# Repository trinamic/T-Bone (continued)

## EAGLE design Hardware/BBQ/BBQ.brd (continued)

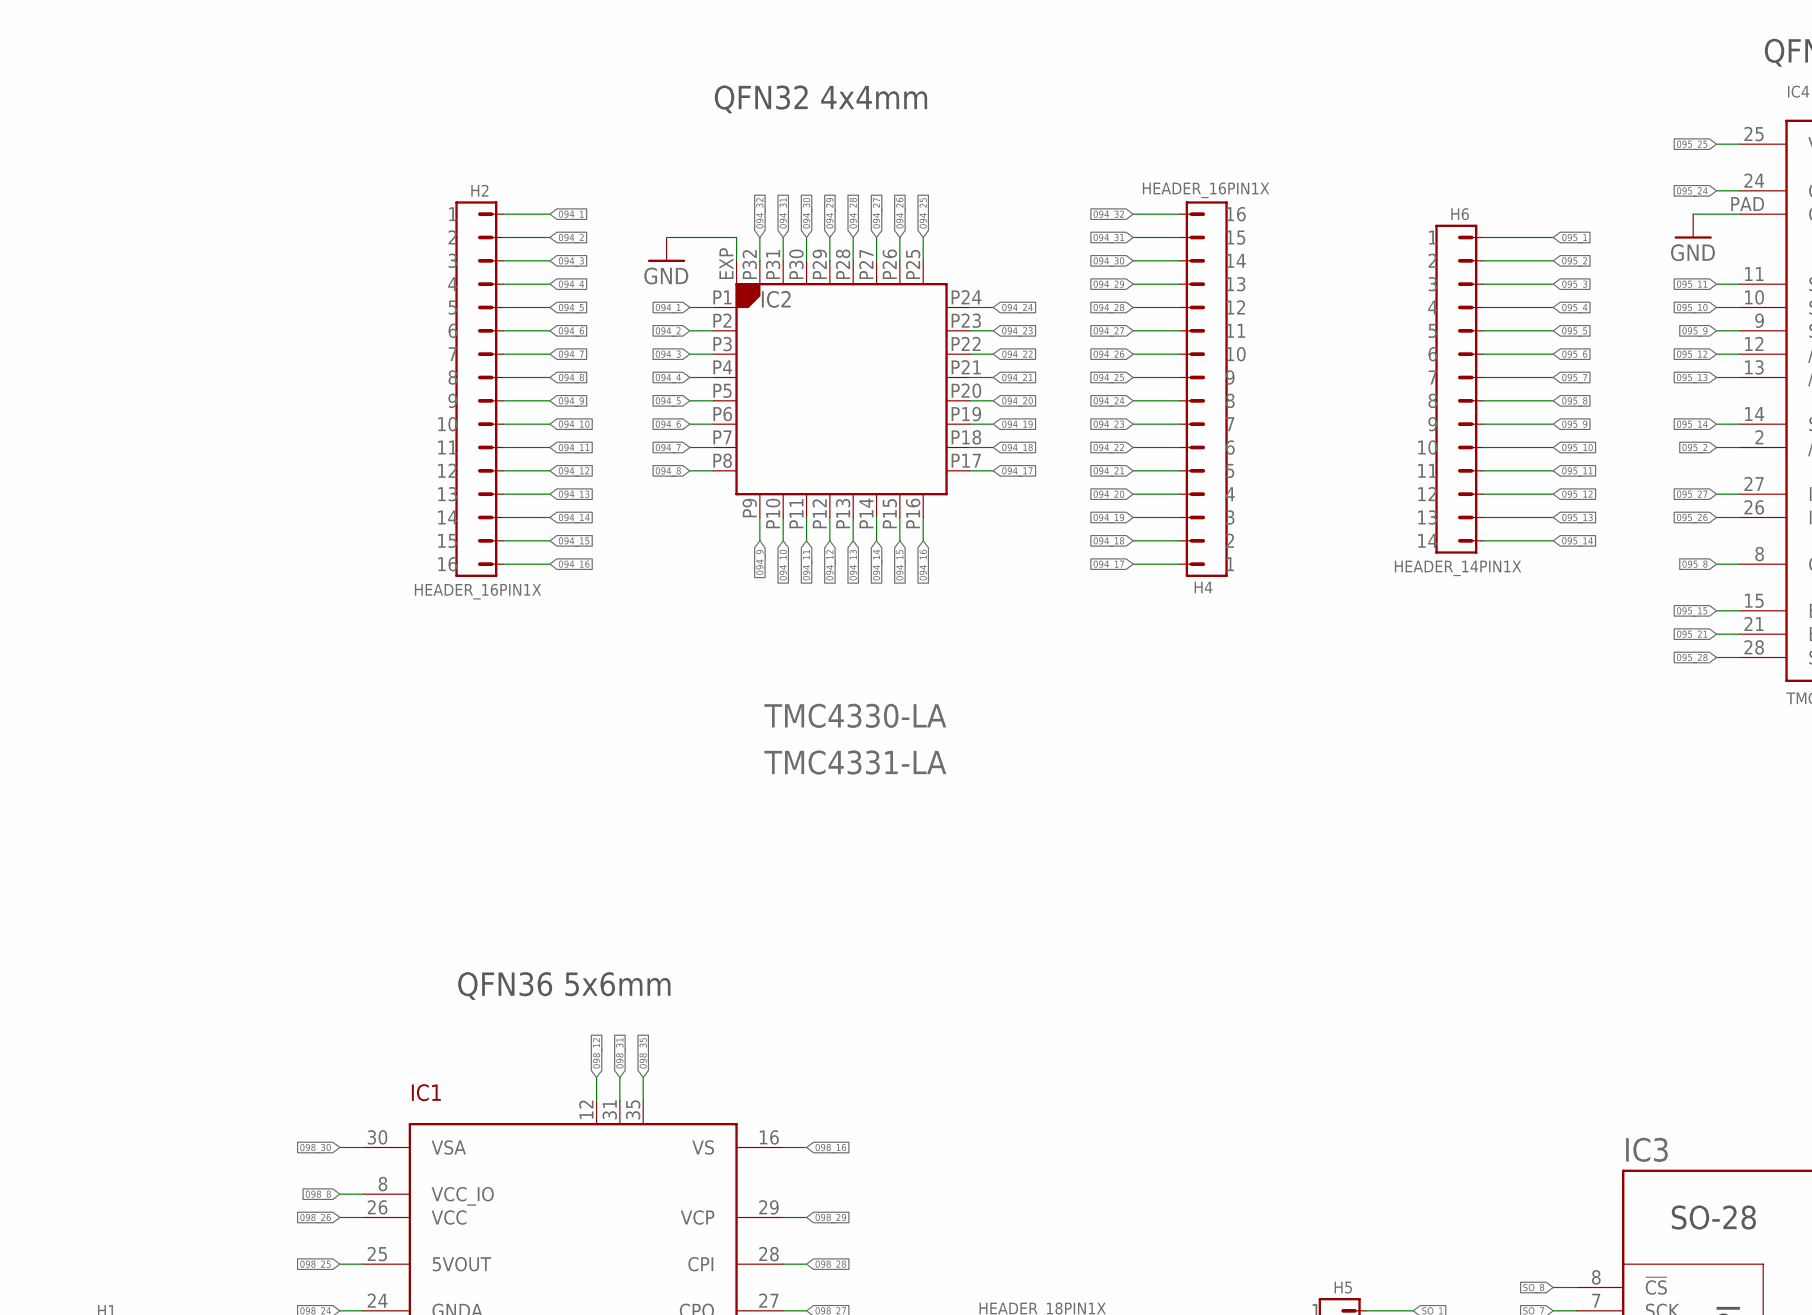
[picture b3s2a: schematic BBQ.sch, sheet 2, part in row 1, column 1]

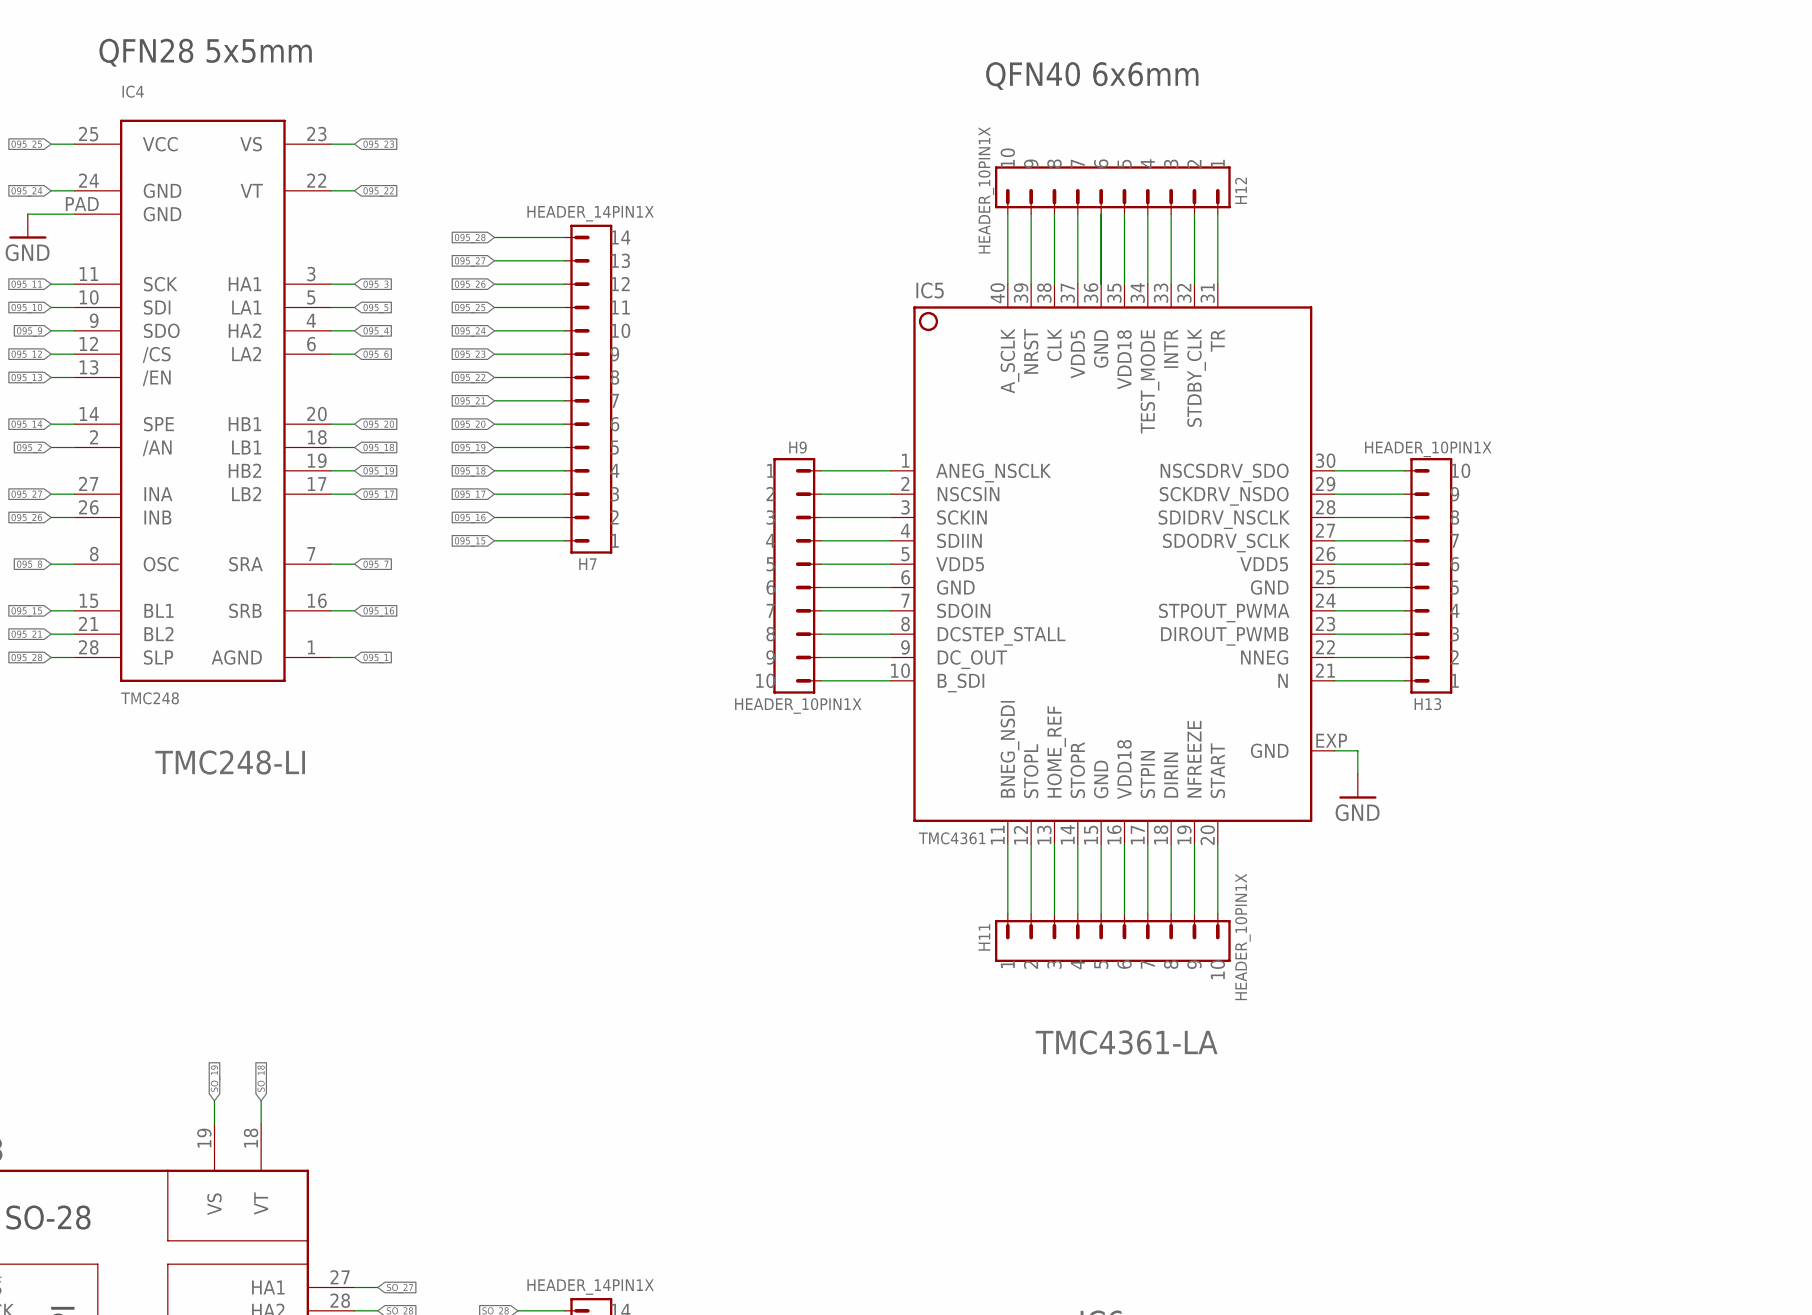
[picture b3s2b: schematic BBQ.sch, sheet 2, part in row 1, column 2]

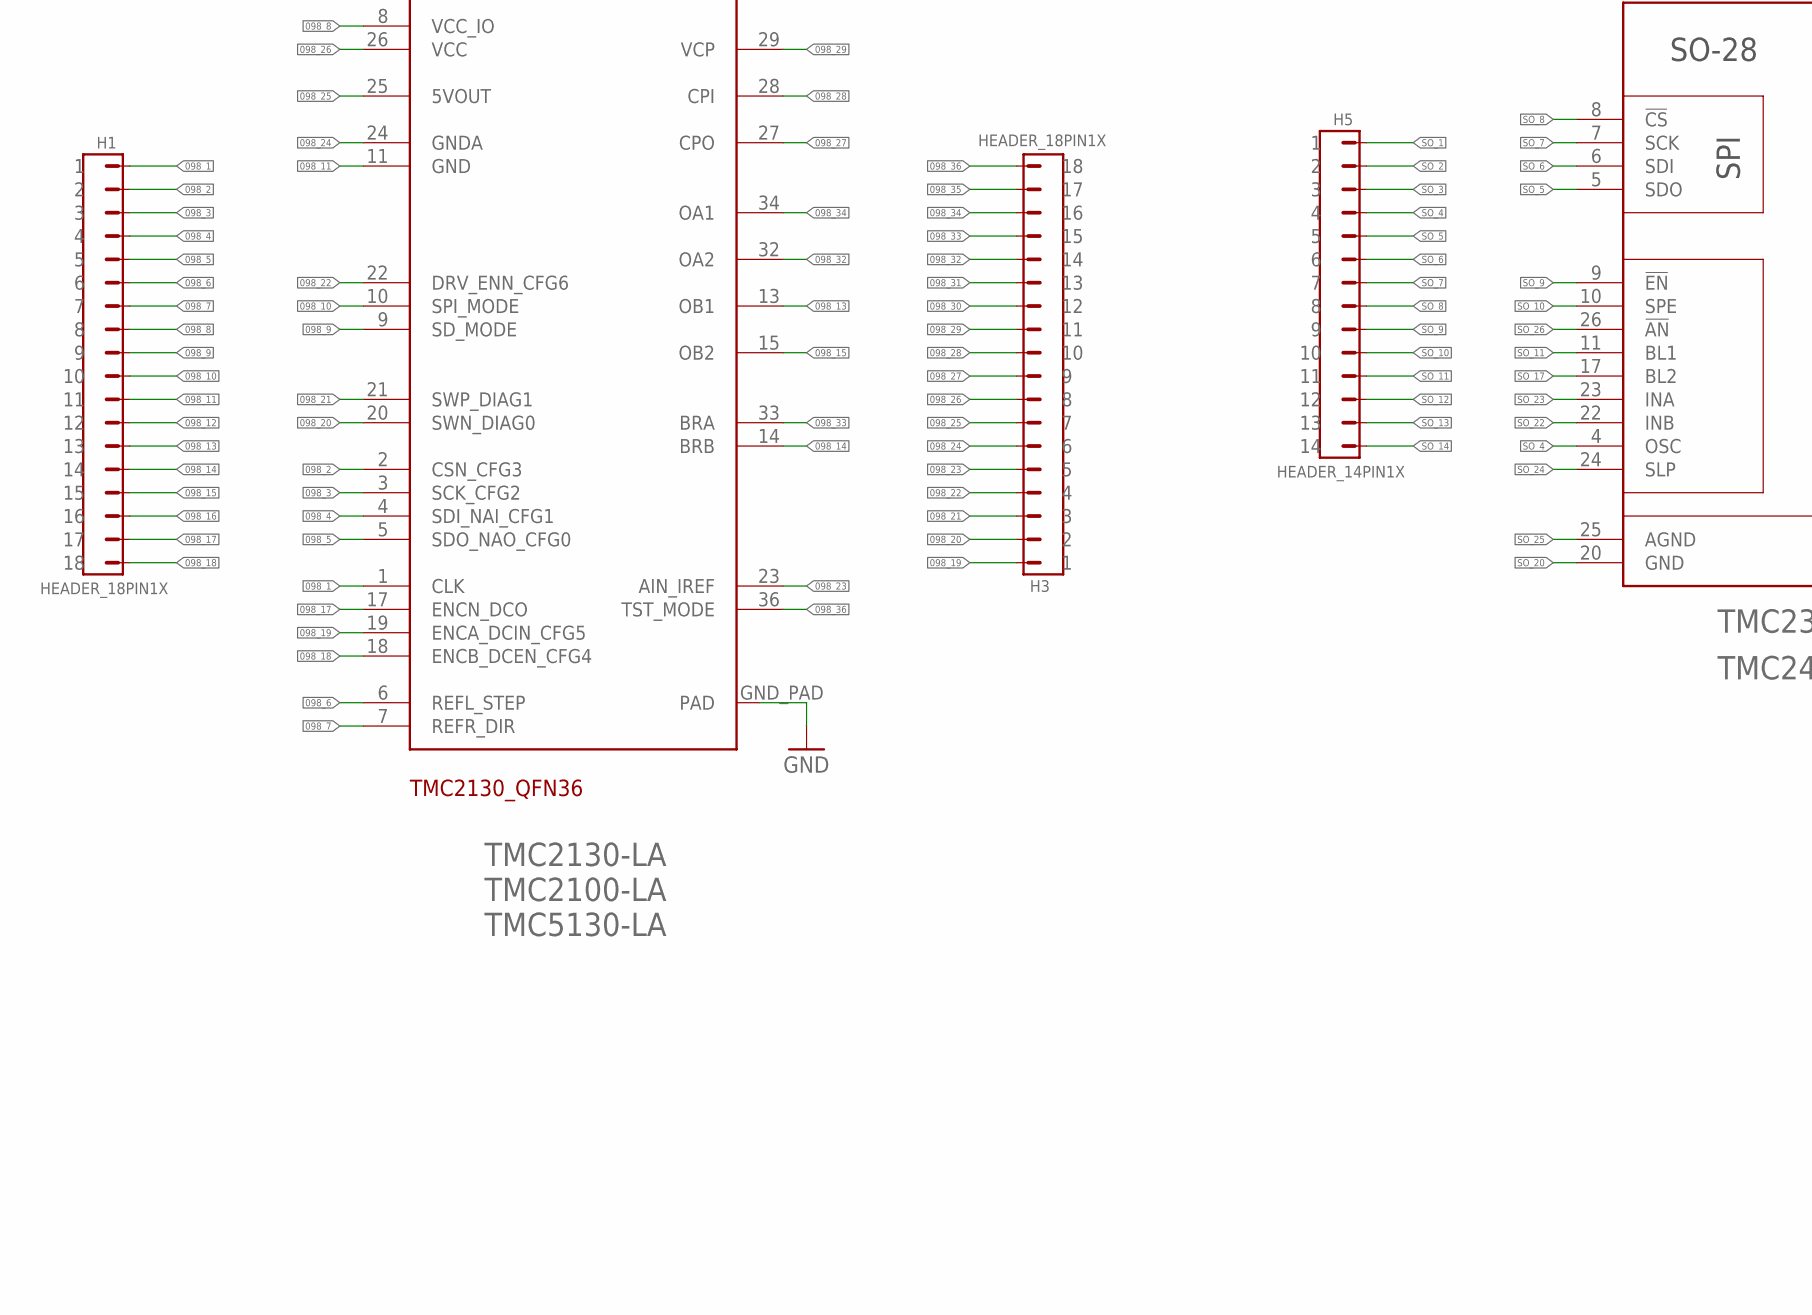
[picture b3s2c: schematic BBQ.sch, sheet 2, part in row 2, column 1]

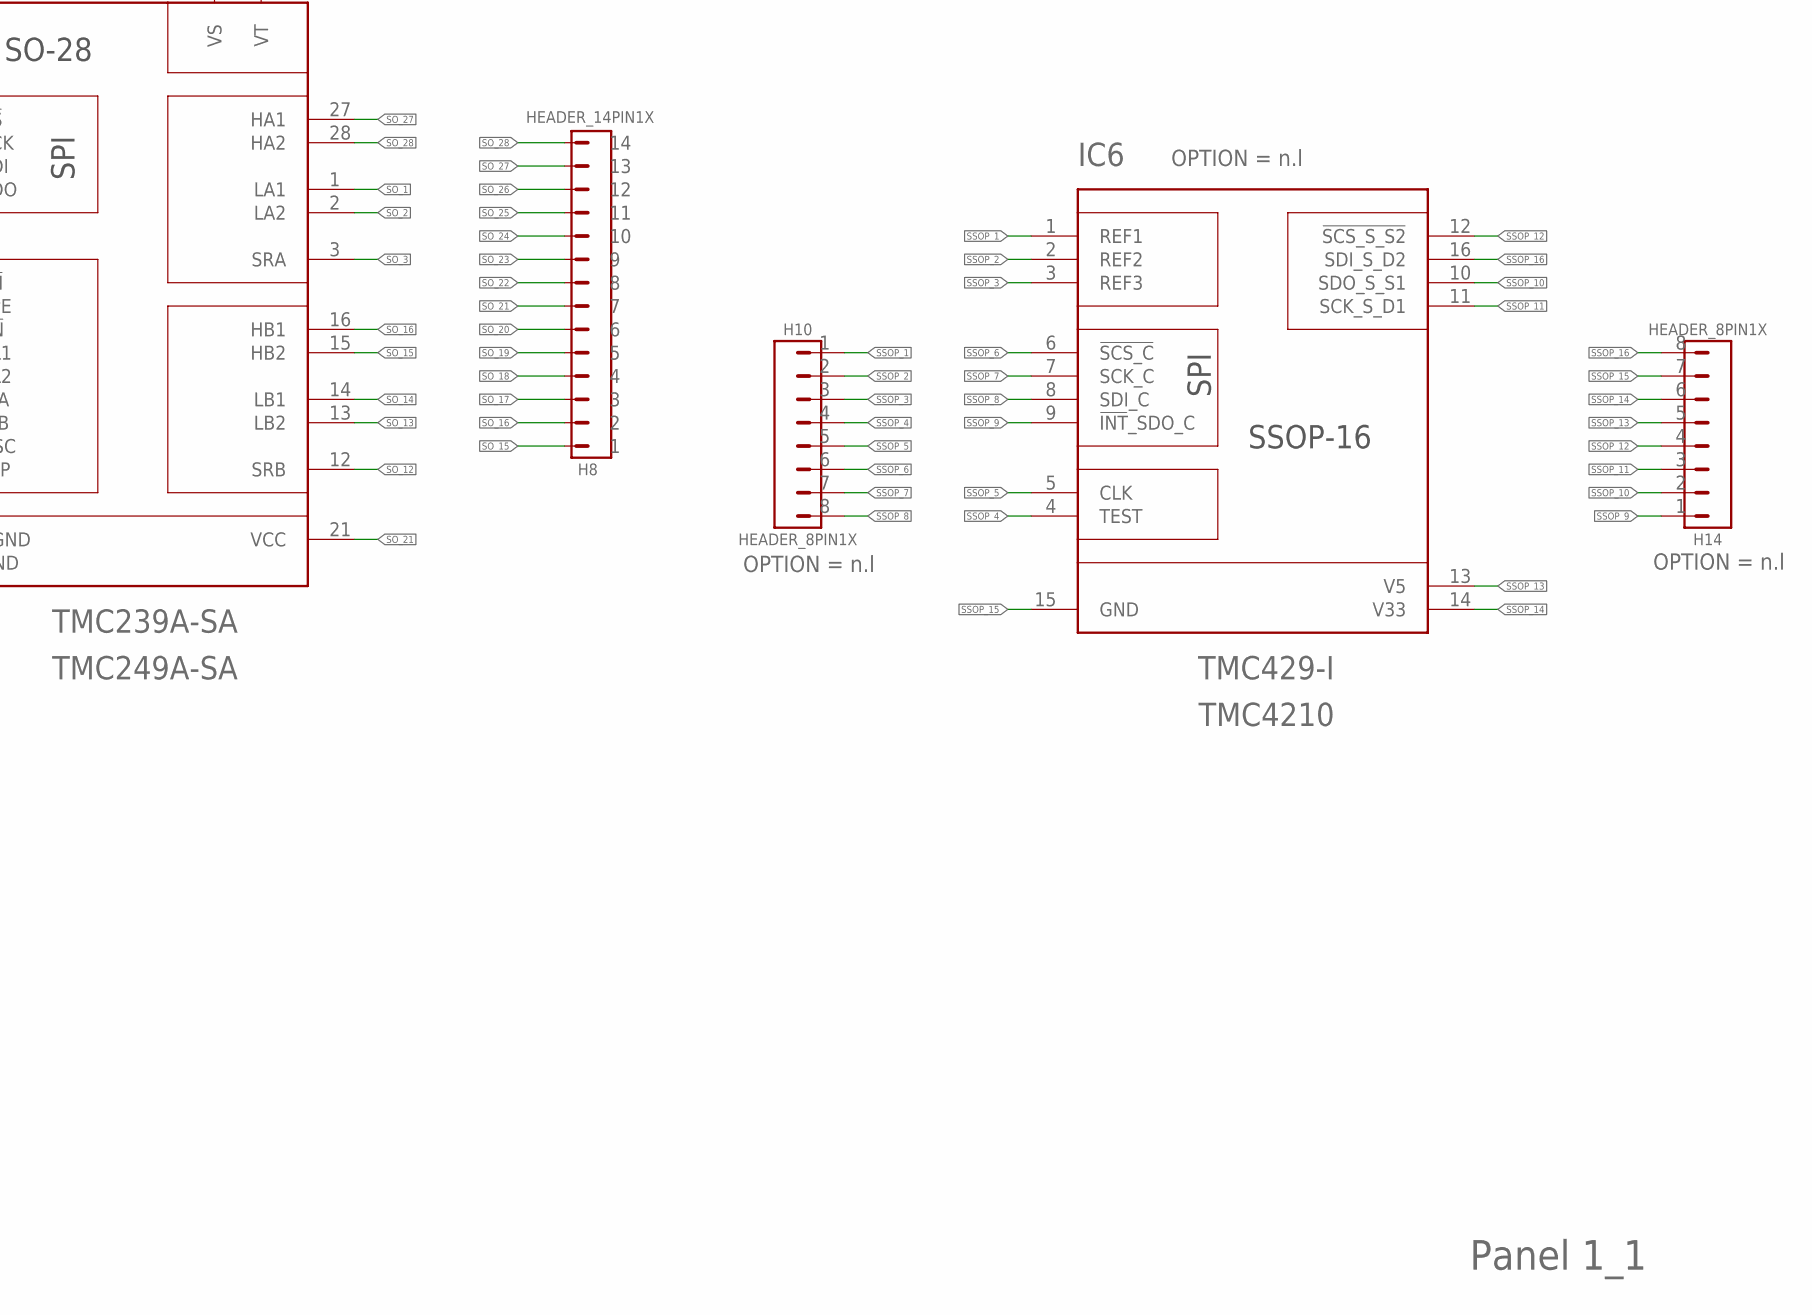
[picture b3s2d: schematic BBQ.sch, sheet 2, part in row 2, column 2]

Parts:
H1, H3: HEADER_18PIN1X; 18PIN_2.54_TH
H2, H4: HEADER_16PIN1X; 16PIN_2.54_TH
H5, H6, H7, H8: HEADER_14PIN1X; 14PIN_2.54_TH
H9, H11, H12, H13: HEADER_10PIN1X; 10PIN_2.54_TH
H10, H14: HEADER_8PIN1X; 8PIN_2.54_TH
IC1: TMC2130_QFN36; QFN36
IC2: TMC4330-LA; QFN-32_4X4
IC3: TMC249A-SA; SO28
IC4: TMC248; QFN28_5X5
IC5: TMC4361; QFN40L
IC6: TMC429-I; SSOP16

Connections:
094_1: H2.1, IC2.P1
094_2: H2.2, IC2.P2
094_3: H2.3, IC2.P3
094_4: H2.4, IC2.P4
094_5: H2.5, IC2.P5
094_6: H2.6, IC2.P6
094_7: H2.7, IC2.P7
094_8: H2.8, IC2.P8
094_9: H2.9, IC2.P9
094_10: H2.10, IC2.P10
094_11: H2.11, IC2.P11
094_12: H2.12, IC2.P12
094_13: H2.13, IC2.P13
094_14: H2.14, IC2.P14
094_15: H2.15, IC2.P15
094_16: H2.16, IC2.P16
094_17: H4.1, IC2.P17
094_18: H4.2, IC2.P18
094_19: H4.3, IC2.P19
094_20: H4.4, IC2.P20
094_21: H4.5, IC2.P21
094_22: H4.6, IC2.P22
094_23: H4.7, IC2.P23
094_24: H4.8, IC2.P24
094_25: H4.9, IC2.P25
094_26: H4.10, IC2.P26
094_27: H4.11, IC2.P27
094_28: H4.12, IC2.P28
094_29: H4.13, IC2.P29
094_30: H4.14, IC2.P30
094_31: H4.15, IC2.P31
094_32: H4.16, IC2.P32
094_GND: IC2.EXP
095_1: H6.1, IC4.1 (AGND)
095_2: H6.2, IC4.2 (/AN)
095_3: H6.3, IC4.3 (HA1)
095_4: H6.4, IC4.4 (HA2)
095_5: H6.5, IC4.5 (LA1)
095_6: H6.6, IC4.6 (LA2)
095_7: H6.7, IC4.7 (SRA)
095_8: H6.8, IC4.8 (OSC)
095_9: H6.9, IC4.9 (SDO)
095_10: H6.10, IC4.10 (SDI)
095_11: H6.11, IC4.11 (SCK)
095_12: H6.12, IC4.12 (/CS)
095_13: H6.13, IC4.13 (/EN)
095_14: H6.14, IC4.14 (SPE)
095_15: H7.1, IC4.15 (BL1)
095_16: H7.2, IC4.16 (SRB)
095_17: H7.3, IC4.17 (LB2)
095_18: H7.4, IC4.18 (LB1)
095_19: H7.5, IC4.19 (HB2)
095_20: H7.6, IC4.20 (HB1)
095_21: H7.7, IC4.21 (BL2)
095_22: H7.8, IC4.22 (VT)
095_23: H7.9, IC4.23 (VS)
095_24: H7.10, IC4.24 (GND)
095_25: H7.11, IC4.25 (VCC)
095_26: H7.12, IC4.26 (INB)
095_27: H7.13, IC4.27 (INA)
095_28: H7.14, IC4.28 (SLP)
095_GND: IC4.PAD (GND)
097_GND: IC5.EXP (GND)
098_1: H1.1, IC1.1 (CLK)
098_2: H1.2, IC1.2 (CSN_CFG3)
098_3: H1.3, IC1.3 (SCK_CFG2)
098_4: H1.4, IC1.4 (SDI_NAI_CFG1)
098_5: H1.5, IC1.5 (SDO_NAO_CFG0)
098_6: H1.6, IC1.6 (REFL_STEP)
098_7: H1.7, IC1.7 (REFR_DIR)
098_8: H1.8, IC1.8 (VCC_IO)
098_9: H1.9, IC1.9 (SD_MODE)
098_10: H1.10, IC1.10 (SPI_MODE)
098_11: H1.11, IC1.11 (GND)
098_12: H1.12, IC1.12
098_13: H1.13, IC1.13 (OB1)
098_14: H1.14, IC1.14 (BRB)
098_15: H1.15, IC1.15 (OB2)
098_16: H1.16, IC1.16 (VS)
098_17: H1.17, IC1.17 (ENCN_DCO)
098_18: H1.18, IC1.18 (ENCB_DCEN_CFG4)
098_19: H3.1, IC1.19 (ENCA_DCIN_CFG5)
098_20: H3.2, IC1.20 (SWN_DIAG0)
098_21: H3.3, IC1.21 (SWP_DIAG1)
098_22: H3.4, IC1.22 (DRV_ENN_CFG6)
098_23: H3.5, IC1.23 (AIN_IREF)
098_24: H3.6, IC1.24 (GNDA)
098_25: H3.7, IC1.25 (5VOUT)
098_26: H3.8, IC1.26 (VCC)
098_27: H3.9, IC1.27 (CPO)
098_28: H3.10, IC1.28 (CPI)
098_29: H3.11, IC1.29 (VCP)
098_30: H3.12, IC1.30 (VSA)
098_31: H3.13, IC1.31
098_32: H3.14, IC1.32 (OA2)
098_33: H3.15, IC1.33 (BRA)
098_34: H3.16, IC1.34 (OA1)
098_35: H3.17, IC1.35
098_36: H3.18, IC1.36 (TST_MODE)
098_GND: IC1.GND_PAD (PAD)
unnamed: H9.1, IC5.1 (ANEG_NSCLK)
unnamed: H9.2, IC5.2 (NSCSIN)
unnamed: H9.3, IC5.3 (SCKIN)
unnamed: H9.4, IC5.4 (SDIIN)
unnamed: H9.5, IC5.5 (VDD5)
unnamed: H9.6, IC5.6 (GND)
unnamed: H9.7, IC5.7 (SDOIN)
unnamed: H9.8, IC5.8 (DCSTEP_STALL)
unnamed: H9.9, IC5.9 (DC_OUT)
unnamed: H9.10, IC5.10 (B_SDI)
unnamed: H11.1, IC5.11 (BNEG_NSDI)
unnamed: H11.2, IC5.12 (STOPL)
unnamed: H11.3, IC5.13 (HOME_REF)
unnamed: H11.4, IC5.14 (STOPR)
unnamed: H11.5, IC5.15 (GND)
unnamed: H11.6, IC5.16 (VDD18)
unnamed: H11.7, IC5.17 (STPIN)
unnamed: H11.8, IC5.18 (DIRIN)
unnamed: H11.9, IC5.19 (NFREEZE)
unnamed: H11.10, IC5.20 (START)
unnamed: H13.1, IC5.21 (N)
unnamed: H13.2, IC5.22 (NNEG)
unnamed: H13.3, IC5.23 (DIROUT_PWMB)
unnamed: H13.4, IC5.24 (STPOUT_PWMA)
unnamed: H13.5, IC5.25 (GND)
unnamed: H13.6, IC5.26 (VDD5)
unnamed: H13.7, IC5.27 (SDODRV_SCLK)
unnamed: H13.8, IC5.28 (SDIDRV_NSCLK)
unnamed: H13.9, IC5.29 (SCKDRV_NSDO)
unnamed: H13.10, IC5.30 (NSCSDRV_SDO)
unnamed: H12.1, IC5.31 (TR)
unnamed: H12.2, IC5.32 (STDBY_CLK)
unnamed: H12.3, IC5.33 (INTR)
unnamed: H12.4, IC5.34 (TEST_MODE)
unnamed: H12.5, IC5.35 (VDD18)
unnamed: H12.6, IC5.36 (GND)
unnamed: H12.7, IC5.37 (VDD5)
unnamed: H12.8, IC5.38 (CLK)
unnamed: H12.9, IC5.39 (NRST)
unnamed: H12.10, IC5.40 (A_SCLK)
SO_1: H5.1, IC3.1 (LA1)
SO_2: H5.2, IC3.2 (LA2)
SO_3: H5.3, IC3.3 (SRA)
SO_4: H5.4, IC3.4 (OSC)
SO_5: H5.5, IC3.5 (SDO)
SO_6: H5.6, IC3.6 (SDI)
SO_7: H5.7, IC3.7 (SCK)
SO_8: H5.8, IC3.8 (!CS)
SO_9: H5.9, IC3.9 (!EN)
SO_10: H5.10, IC3.10 (SPE)
SO_11: H5.11, IC3.11 (BL1)
SO_12: H5.12, IC3.12 (SRB)
SO_13: H5.13, IC3.13 (LB2)
SO_14: H5.14, IC3.14 (LB1)
SO_15: H8.1, IC3.15 (HB2)
SO_16: H8.2, IC3.16 (HB1)
SO_17: H8.3, IC3.17 (BL2)
SO_18: H8.4, IC3.18 (VT)
SO_19: H8.5, IC3.19 (VS)
SO_20: H8.6, IC3.20 (GND)
SO_21: H8.7, IC3.21 (VCC)
SO_22: H8.8, IC3.22 (INB)
SO_23: H8.9, IC3.23 (INA)
SO_24: H8.10, IC3.24 (SLP)
SO_25: H8.11, IC3.25 (AGND)
SO_26: H8.12, IC3.26 (!AN)
SO_27: H8.13, IC3.27 (HA1)
SO_28: H8.14, IC3.28 (HA2)
SSOP_1: H10.1, IC6.1 (REF1)
SSOP_2: H10.2, IC6.2 (REF2)
SSOP_3: H10.3, IC6.3 (REF3)
SSOP_4: H10.4, IC6.4 (TEST)
SSOP_5: H10.5, IC6.5 (CLK)
SSOP_6: H10.6, IC6.6 (!SCS_C)
SSOP_7: H10.7, IC6.7 (SCK_C)
SSOP_8: H10.8, IC6.8 (SDI_C)
SSOP_9: H14.1, IC6.9 (!INT!_SDO_C)
SSOP_10: H14.2, IC6.10 (SDO_S_S1)
SSOP_11: H14.3, IC6.11 (SCK_S_D1)
SSOP_12: H14.4, IC6.12 (!SCS_S_S2)
SSOP_13: H14.5, IC6.13 (V5)
SSOP_14: H14.6, IC6.14 (V33)
SSOP_15: H14.7, IC6.15 (GND)
SSOP_16: H14.8, IC6.16 (SDI_S_D2)

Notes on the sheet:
Panel 1_1
TMC4210
SSOP-16
TMC239A-SA
SO-28
TMC4330-LA
QFN32 4x4mm
TMC4331-LA
TMC248-LI
QFN28 5x5mm
TMC4361-LA
QFN40 6x6mm
TMC2130-LA TMC2100-LA TMC5130-LA
QFN36 5x6mm
